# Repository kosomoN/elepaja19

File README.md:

## Lab power supply

This repository contains firmware and PCB designs for a lab power supply designed by Onni Kosomaa, Jere Mielty and Juha Rauhala.

### Repository contents

| Folder                     | Contents                                           |
| -------------------------- | -------------------------------------------------- |
| [components](components)   | Custom KiCad component used in the schematics.     |
| [control_mc](control_mc)   | The regulator MCU firmware.                        |
| [pcb_1](pcb_1)             | The main regulator PCB KiCad project.              |
| [pcb_PiHat](pcb_PiHat)     | The Raspberry Pi Zero extension PCB KiCad project. |
| [pcb_fpanel](pcb_fpanel)   | The main front panel keyboard PCB.                 |
| [pcb_fpanel2](pcb_fpanel2) | The auxiliary front panel keyboard PCB.            |
| [ui](ui)                   | UI software running on the Raspberry Pi.           |

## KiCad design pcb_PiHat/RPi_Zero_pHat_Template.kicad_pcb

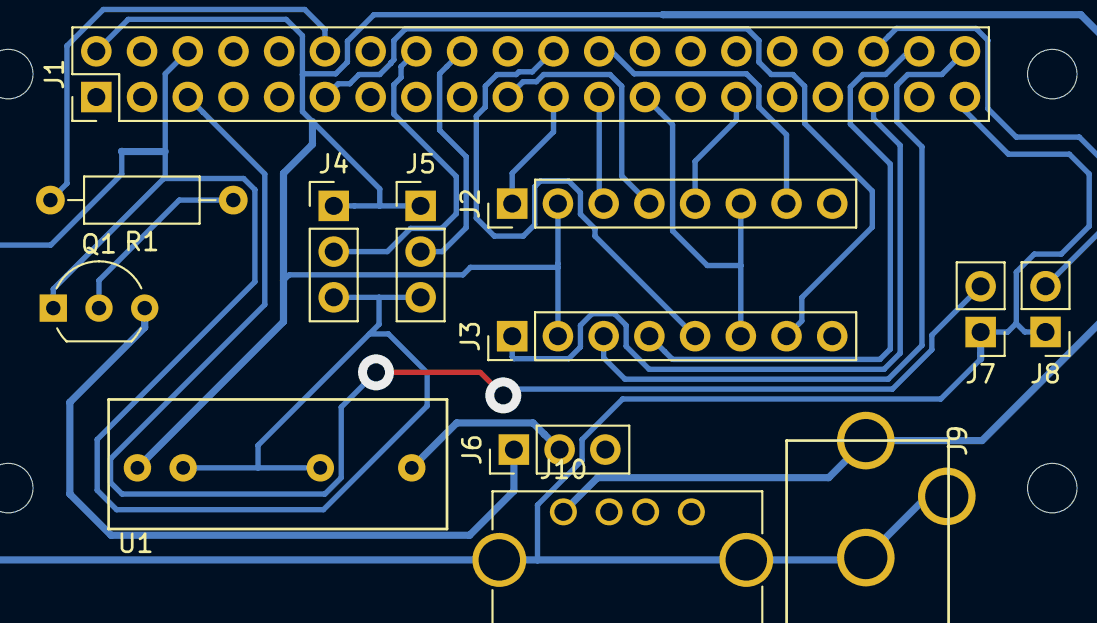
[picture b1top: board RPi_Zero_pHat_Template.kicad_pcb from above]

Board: 2 copper layers, 13 parts (0 on the bottom side), 20 nets.

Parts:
J1: RPi_GPIO; PinHeader_2x20_P2.54mm_Vertical
J2, J3: Isolated_ISP; PinHeader_1x08_P2.54mm_Vertical
J4, J5: Conn_Relay; PinHeader_1x03_P2.54mm_Vertical
J6: Conn_01x03; Pin_Header_Straight_1x03_Pitch2.54mm
J7, J8: Conn_switch; Pin_Header_Straight_1x02_Pitch2.54mm
J9: 5V_in; 5V_power
J10: USB_A
Q1: Q_NPN_EBC; TO-92_Inline_Wide
R1: R; R_Axial_DIN0207_L6.3mm_D2.5mm_P10.16mm_Horizontal
U1: SPUN02L-12

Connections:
GND: J1.6, J1.9, J1.14, J1.20, J1.25, J1.30, J1.34, J1.39, J2.6, J3.6, J4.3, J5.3, J7.1, J8.1, J9.2, J10.4, J10.5, Q1.1, U1.2, U1.5
unnamed: J1.2, J2.2, J3.2, J4.1, J5.1, J9.1, J10.1, U1.1
unnamed: J1.5, J7.2
unnamed: J1.11, J3.7
unnamed: J1.12, R1.2
unnamed: J1.16, J4.2
unnamed: J1.18, J5.2
unnamed: J1.19, J2.4
unnamed: J1.21, J2.1
unnamed: J1.22, J3.5
unnamed: J1.23, J2.3
unnamed: J1.24, J2.7
unnamed: J1.29, J2.5
unnamed: J1.35, J3.1
unnamed: J1.36, J8.2
unnamed: J1.38, J3.4
unnamed: J1.40, J3.3
unnamed: J6.1, Q1.3
unnamed: J6.2, U1.7
unnamed: Q1.2, R1.1

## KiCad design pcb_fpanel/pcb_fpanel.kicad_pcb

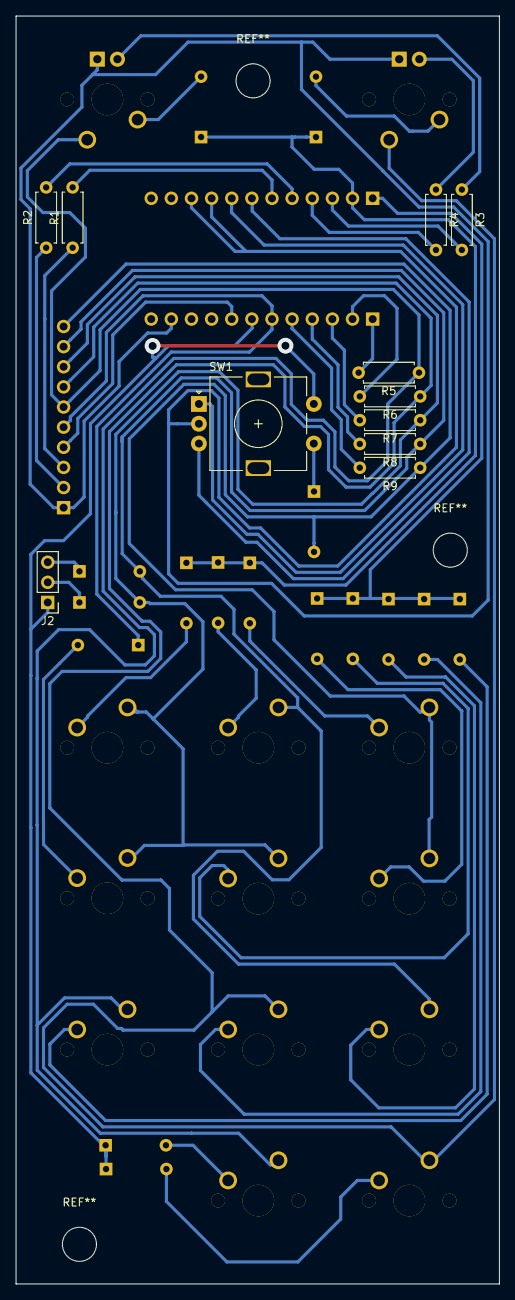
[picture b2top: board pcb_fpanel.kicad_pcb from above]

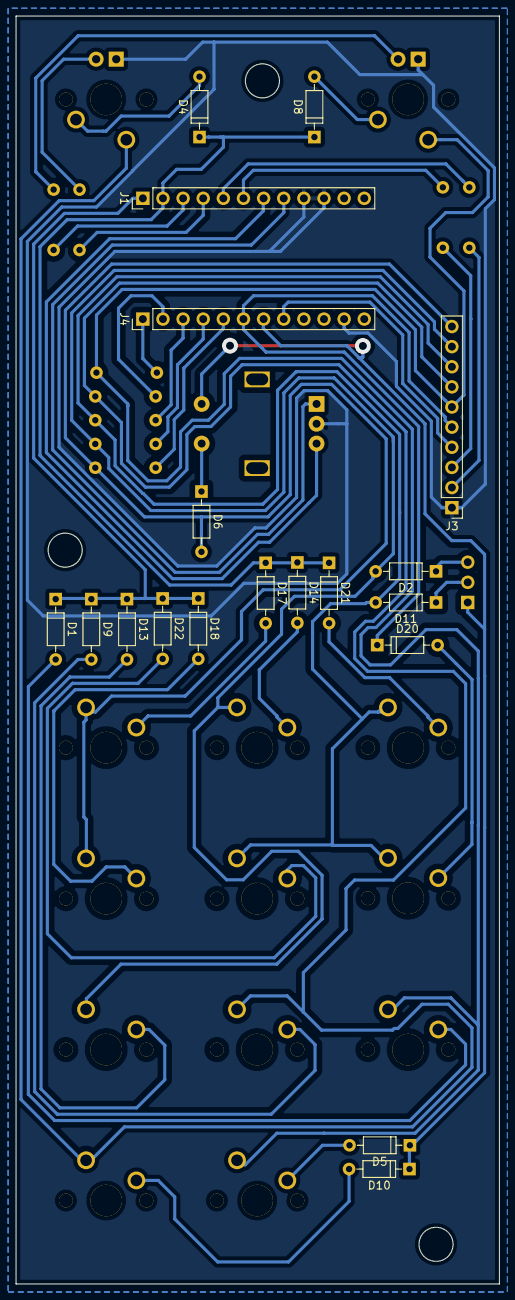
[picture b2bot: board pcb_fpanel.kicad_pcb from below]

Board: 2 copper layers, 61.0 x 160.0 mm, 43 parts (19 on the bottom side), 40 nets.

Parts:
D1, D2, D4, D5, D6, D8, D9, D10, D11, D13, D14, D17, D18, D20, D21, D22: D; D_DO-35_SOD27_P7.62mm_Horizontal
J1, J4: Conn_01x12; Pin_Header_Straight_1x12_Pitch2.54mm
J2: Conn_01x03; Pin_Header_Straight_1x03_Pitch2.54mm
J3: Conn_01x10; Pin_Header_Straight_1x10_Pitch2.54mm
R1, R2, R3, R4, R5, R6, R7, R8, R9: R; R_Axial_DIN0207_L6.3mm_D2.5mm_P7.62mm_Horizontal
SW1: Rotary_Encoder_Switch; RotaryEncoder_Alps_EC11E-Switch_Vertical_H20mm
SW3, SW8: SW_Push_LED; MXOnly-1U
SW4, SW5, SW9, SW10, SW13, SW14, SW17, SW18, SW20, SW21, SW22: SW_Push_LED; MXOnly-1U-NoLED

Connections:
GNDD: J1.9, J1.10, J3.1, J4.11, SW1.C
unnamed: D1.2, SW4.1
unnamed: D2.1, J2.3
unnamed: D4.2, SW3.1
unnamed: D5.2, SW5.1
unnamed: D8.2, SW8.1
unnamed: D9.2, SW9.1
unnamed: D10.2, SW10.1
unnamed: D11.1, J2.2
unnamed: D13.2, SW14.1
unnamed: D14.2, SW13.1
unnamed: D17.2, SW17.1
unnamed: D18.2, SW18.1
unnamed: D20.2, SW20.1
unnamed: D21.2, SW21.1
unnamed: D22.2, SW22.1
unnamed: J1.3, R3.2
unnamed: J1.4, R4.2
unnamed: J1.5, R2.2
unnamed: J1.6, R1.2
unnamed: J1.7, SW1.B
unnamed: J1.8, SW1.A
unnamed: J4.1, R5.2
unnamed: J4.2, R6.2
unnamed: J4.3, R7.2
unnamed: J4.4, R8.2
unnamed: J4.5, R9.2
column_1: J3.6, R5.1, SW4.2, SW5.2, SW8.2
column_2: J3.7, R6.1, SW3.2, SW9.2, SW10.2
column_3: D2.2, J3.9, R8.1, SW13.2, SW14.2
column_4: D6.2, J3.10, R9.1, SW17.2, SW18.2
column_5: D11.2, J3.8, R7.1, SW20.2, SW21.2, SW22.2
encoder_button: D6.1, SW1.S1
led_1: J3.3, R1.1
led_2: J3.2, R2.1
row_1: J3.4, J4.8
row_2: D20.1, J3.5, J4.6
row_3: D4.1, D8.1, D14.1, D17.1, D21.1, J1.2
row_4: D1.1, D9.1, D13.1, D18.1, D22.1, J1.1
row_5: D5.1, D10.1, J2.1, J4.7, SW1.S2

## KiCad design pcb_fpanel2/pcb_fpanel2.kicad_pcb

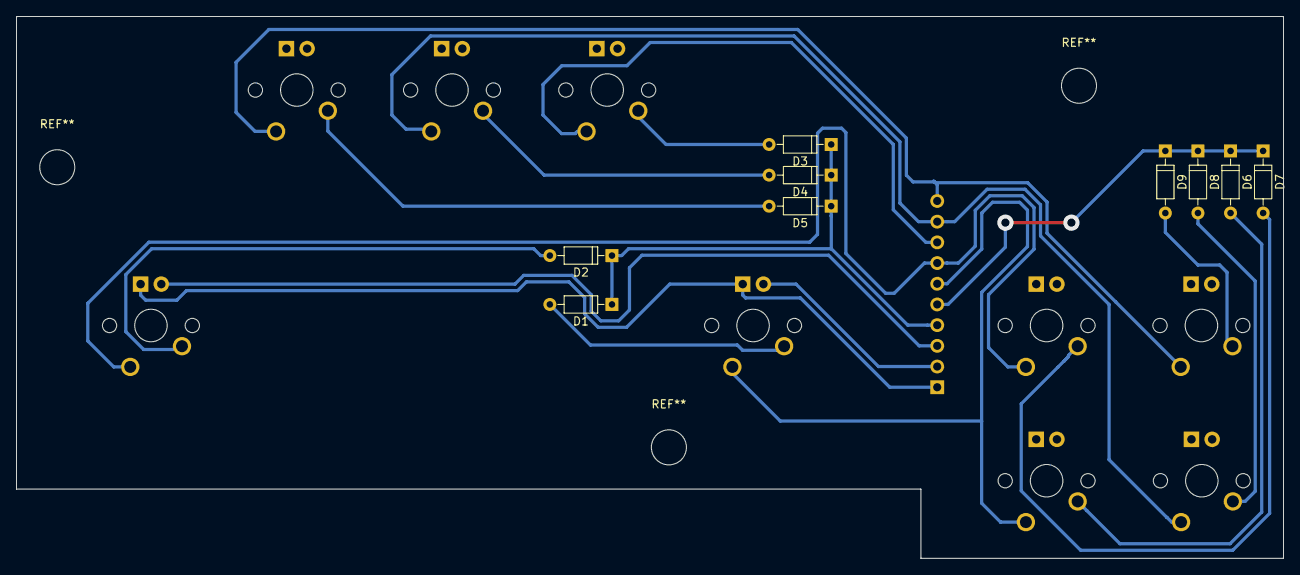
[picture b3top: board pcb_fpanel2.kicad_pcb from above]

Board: 2 copper layers, 155.5 x 66.5 mm, 19 parts (1 on the bottom side), 19 nets.

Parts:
D1, D2, D3, D4, D5, D6, D7, D8, D9: D; D_DO-35_SOD27_P7.62mm_Horizontal
J1: Conn_01x10; Pin_Header_Straight_1x10_Pitch2.54mm
SW1, SW2, SW3, SW4, SW5, SW6, SW7, SW8, SW9: SW_Push_LED; MXOnly-1U

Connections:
GNDD: J1.1, SW1.4, SW2.4
unnamed: D1.2, SW1.1
unnamed: D2.2, SW2.1
unnamed: D3.2, SW3.1
unnamed: D4.2, SW4.1
unnamed: D5.2, SW5.1
unnamed: D6.2, SW6.1
unnamed: D7.2, SW7.1
unnamed: D8.2, SW8.1
unnamed: D9.2, SW9.1
column_1: J1.6, SW1.2, SW6.2
column_2: J1.7, SW2.2, SW7.2
column_3: J1.9, SW4.2, SW8.2
column_4: J1.10, SW5.2, SW9.2
column_5: J1.8, SW3.2
led_1: J1.3, SW2.3
led_2: J1.2, SW1.3
row_1: D1.1, D2.1, D3.1, D4.1, D5.1, J1.4
row_2: D6.1, D7.1, D8.1, D9.1, J1.5

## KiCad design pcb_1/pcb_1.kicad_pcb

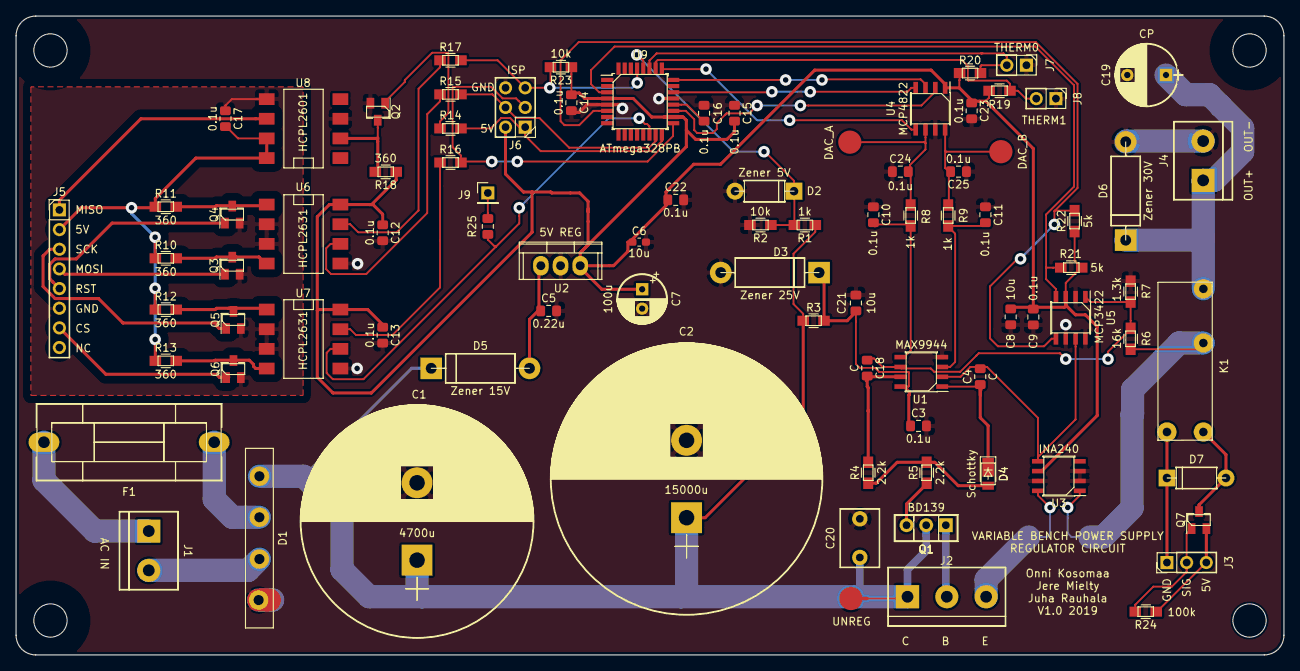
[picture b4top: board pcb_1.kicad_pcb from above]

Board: 2 copper layers, 163.8 x 82.6 mm, 88 parts (1 on the bottom side), 58 nets.

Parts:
C1: 4700u; CP_Radial_D30.0mm_P10.00mm_SnapIn
C2: 15000u; CP_Radial_D35.0mm_P10.00mm_SnapIn
C3, C9, C10, C11, C12, C13, C14, C15, C16, C17, C22, C23, C24, C25: 0.1u; C_0805_2012Metric_Pad1.15x1.40mm_HandSolder
C4, C18: C; C_0805_2012Metric_Pad1.15x1.40mm_HandSolder
C5: 0.22u; C_0805_2012Metric_Pad1.15x1.40mm_HandSolder
C6: 10u; C_0603_1608Metric_Pad1.05x0.95mm_HandSolder
C7: 100u; CP_Radial_D6.3mm_P2.50mm
C8, C21: 10u; C_0805_2012Metric_Pad1.15x1.40mm_HandSolder
C19: CP; CP_Radial_D8.0mm_P5.00mm
C20: C; C_Disc_D7.5mm_W5.0mm_P5.00mm
D1: D_Bridge_+AA-; GBU6D_diode-bridge
D2: Zener 5V; D_DO-41_SOD81_P7.62mm_Horizontal
D3: Zener 25V; D_5W_P12.70mm_Horizontal
D4: Schottky; D_PowerDI-123
D5: Zener 15V; D_5W_P12.70mm_Horizontal
D6: Zener 30V; D_5W_P12.70mm_Horizontal
D7: D; D_DO-41_SOD81_P7.62mm_Horizontal
F1: Fuse; Fuseholder5x20_horiz_SemiClosed_Casing10x25mm
J1, J4: Screw_Terminal_01x02; TerminalBlock_bornier-2_P5.08mm
J2: Screw_Terminal_01x03; TerminalBlock_bornier-3_P5.08mm
J3: Conn_Relay; Pin_Header_Straight_1x03_Pitch2.54mm
J5: Isolated_ISP; Pin_Header_Straight_1x08_Pitch2.54mm
J6: AVR-ISP-6; Pin_Header_Straight_2x03_Pitch2.54mm
J7: THERM0; Pin_Header_Straight_1x02_Pitch2.54mm
J8: THERM1; Pin_Header_Straight_1x02_Pitch2.54mm
J9: CS; PinHeader_1x01_P2.54mm_Vertical
K1: DIPxx-1Axx-11x; PCJ-105D3MH
Q1: BD139; TO-126_Vertical
Q2, Q3, Q4, Q5, Q6, Q7: Q_NMOS_GSD; SuperSOT-3
R1, R8, R9: 1k; R_0805_HandSoldering
R2, R23: 10k; R_0805_HandSoldering
R3, R19, R20: R; R_0805_HandSoldering
R4, R5: 2.2k; R_0805_HandSoldering
R6: 16k; R_0805_HandSoldering
R7: 1.3k; R_0805_HandSoldering
R10, R11, R12, R13, R18: 360; R_0805_HandSoldering
R14, R15, R16, R17: 100; R_0805_HandSoldering
R21, R22: 5k; R_0805_HandSoldering
R24: 100k; R_0805_HandSoldering
R25: 100; R_0805_2012Metric_Pad1.15x1.40mm_HandSolder
Rs1: 0.1; R_2512_HandSoldering
TP1: UNREG; Measurement_Point_Round-SMD-Pad_Big
TP2: DACa; Measurement_Point_Round-SMD-Pad_Big
TP3: DACb; Measurement_Point_Round-SMD-Pad_Big
U1: MAX9944; SOIC-8_3.9x4.9mm_Pitch1.27mm
U2: 5V REG; TO-220
U3: INA240; SOIC-8_3.9x4.9mm_Pitch1.27mm
U4: MCP4822; SOIC-8_3.9x4.9mm_Pitch1.27mm
U5: MCP3422; SOIC-8_3.9x4.9mm_Pitch1.27mm
U6, U7: HCPL2631; HCPL2631SD
U8: HCPL2601; HCPL2631SD
U9: ATmega328PB; TQFP-32_7x7mm_Pitch0.8mm

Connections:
+5V: C6.1, C7.1, C8.1, C9.2, C12.1, C13.1, C14.1, C15.2, C22.1, C23.1, J6.2, R18.1, R19.1, R20.1, R21.1, R22.1, R23.1, U2.3, U3.6, U4.1, U5.3, U6.8, U7.8, U9.4, U9.18
ADC_SCL: R22.2, U5.5, U9.6
ADC_SDA: R21.2, U5.4, U9.3
DAC_CS: U4.2, U9.19
DAC_LDAC: U4.5, U9.25
DAC_SCK: U4.3, U9.24
DAC_SDI: U4.4, U9.22
GNDA: C1.2, C2.2, C3.2, C5.2, C6.2, C7.2, C8.2, C9.1, C10.1, C11.1, C12.2, C13.2, C14.2, C15.1, C16.2, C19.2, C20.2, C21.2, C22.2, C23.2, C24.1, C25.1, D1.4, D2.2, D3.2, D6.2, J4.2, J6.6, J7.1, J8.1, Q2.2, R2.2, R7.2, U1.4, U2.2, U3.2, U3.3, U3.7, U4.7, U5.2, U5.6, U5.8, U6.5, U7.5, U8.3, U9.5, U9.21
Imon: C4.2, U1.2, U3.5, U5.7
Iset: C11.2, R9.1, U1.3
unnamed: C1.1, C2.1, C20.1, D1.1, D5.1, J2.1, Q1.2, R1.1, R3.1, TP1.1
unnamed: C4.1, D4.1, U1.1
unnamed: C5.1, D5.2, U2.1
unnamed: C16.1, U9.20
unnamed: C17.1, J5.6, Q3.2, Q4.2, Q5.2, Q6.2, U6.2, U6.3, U7.2, U7.3, U8.5
unnamed: C17.2, J5.2, R10.1, R11.1, R12.1, R13.1, U8.7, U8.8
unnamed: C18.2, R4.2, U1.7
unnamed: C19.1, D6.1, J4.1, K1.7
unnamed: C3.1, C21.1, D3.1, R3.2, U1.8
unnamed: C24.2, R8.2, TP2.1, U4.6
unnamed: C25.2, R9.2, TP3.1, U4.8
unnamed: D1.2, F1.1
unnamed: D1.3, J1.2
unnamed: D4.2, R4.1, R5.2
unnamed: D7.1, J3.1, K1.2
unnamed: D7.2, K1.6, Q7.3
unnamed: F1.2, J1.1
unnamed: J2.2, Q1.1
unnamed: J2.3, Rs1.1, U3.8
unnamed: J3.2, Q7.1, R24.2
unnamed: J3.3, Q7.2, R24.1
unnamed: J5.1, U8.6
unnamed: J5.3, Q5.1
unnamed: J5.4, Q3.1
unnamed: J5.5, Q4.1
unnamed: J5.7, Q6.1
unnamed: J6.1, R14.2, U9.16
unnamed: J6.3, R16.2, U9.17
unnamed: J6.4, R15.2, U9.15
unnamed: J6.5, R17.2, R23.2, U9.29
unnamed: J7.2, R20.2, U9.27
unnamed: J8.2, R19.2, U9.26
unnamed: J9.1, R25.1
unnamed: K1.1, R6.1, Rs1.2, U3.1
unnamed: Q1.3, R5.1
unnamed: Q2.3, R18.2, U8.2
unnamed: Q3.3, R10.2, U6.4
unnamed: Q4.3, R11.2, U6.1
unnamed: Q5.3, R12.2, U7.1
unnamed: Q6.3, R13.2, U7.4
SLAVE_CS: R25.2, U7.6, U9.14
SLAVE_MISO: Q2.1, R14.1
SLAVE_MOSI: R15.1, U6.6
SLAVE_RESET: R17.1, U6.7
SLAVE_SCK: R16.1, U7.7
UNREG_MON: D2.1, R1.2, R2.1, U9.28
Vmon: C18.1, R6.2, R7.1, U1.6, U5.1
Vset: C10.2, R8.1, U1.5

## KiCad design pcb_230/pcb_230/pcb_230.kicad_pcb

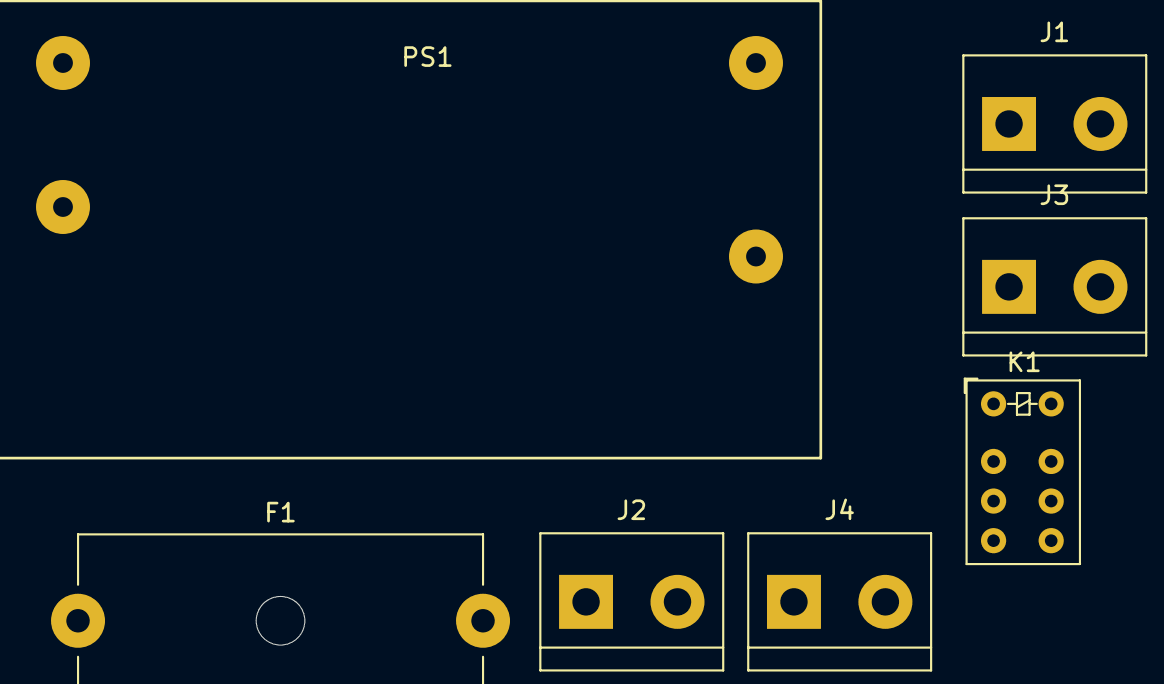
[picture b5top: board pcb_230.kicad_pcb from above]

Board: 2 copper layers, 7 parts (0 on the bottom side), 8 nets, no tracks yet.

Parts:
F1: Fuse; Fuseholder5x20_horiz_open_Schurter_0031_8201
J1, J2, J3, J4: Screw_Terminal_01x02; TerminalBlock_bornier-2_P5.08mm
K1: AZ850P1-x; Relay_DPDT_AXICOM_IMSeries_Pitch3.2mm
PS1: HLK-PM01; IRM-05_ACDC

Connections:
unnamed: F1.1, K1.3, PS1.1
unnamed: F1.2, J1.2
unnamed: J1.1, K1.8, PS1.2
unnamed: J2.2, K1.1
unnamed: J3.1, PS1.4
unnamed: J3.2, PS1.3
unnamed: J4.1, K1.4
unnamed: J4.2, K1.7

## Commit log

2019-10-18 KiCad.gitignore lisätty
2019-10-18 KiCad projekti aloitettu
2019-10-18 Komponenttitiedostot lisätty
2019-10-19 Transistor_BJT-file poistettu tarpeettomana
2019-10-19 Mittauspinnit lisätty
2019-10-19 AC-input lisätty Footprintit mikropiireille
2019-10-19 -Tasasuuntaajalle footprint footprints kansiossa -Oparille lisätty kapasitpanssipaikkoja
2019-10-20 pcb suunniteltu
2019-10-20 .gitignore tiedoston nimi korjattu
2019-10-20 Muuta Library pathit suhteellisiksi
2019-10-22 Oparin regu vaihdettu ja konkkien footprintejä muutettu
2019-10-22 UI Raylib pohja lisätty
    Lisää Makefile:in Raspberry PI:lle, Linuxille sekä Windowsille.
    Lisää myös Visual Studio 2017 projektin.
    Makefile sekä VS2017 etsii oletuksena Raylibiä
    elepaja19/../raylib kansiosta.
2019-10-24 Traceja paksunnettu
2019-10-27 Säätömikrokontrollerin Makefile-pohja
2019-10-28 INA240 kotelo vaihdettu ja toinen vastaava vahvistin poistettu
2019-10-29 Footprintteja muutettu oikeiksi
2019-10-30 pcb:ssa nyt smd- ja tht-komponentit eri puolilla
2019-10-31 30.10 syövytetty pcb
2019-11-10 control_mc: Add communicat:ion pins configuration
2019-11-12 pcb: Add first version with a MCU
    Also update the Kicad project to Kicad version 5
2019-11-13 pcb: Add relay and filtering capacitors
2019-11-14 pcb: Fix mismatching global labels
    Also add connections for thermistors.
2019-11-14 pcb: Add Zener regulator to op-amp supply
2019-11-16 control_mc: Fix line endings in constants.h
2019-11-16 control_mc: Add DAC interfacing code
2019-11-16 Footprintit asetettu ja pcb layout aloitettu
2019-11-16 Footprintit lisätty ja pcb-layout aloitettu
2019-11-16 Komponentit aseteltu paikoilleen ja vähän traceja vedelty
2019-11-17 pcb: Releen ohjauspiiri lisätty
2019-11-17 pcb: Kaikki vedot tehty
2019-11-17 pcb_PiHat: Pi Hatin ensimmäinen versio lisätty
2019-11-17 pcb_PiHat: Relee headeri lisätty
2019-11-17 Toinen konkka lisätty
2019-11-17 pcb: Rescue kirjasto poistettu
2019-11-17 pcb: Suodatuskonkat ja kiinnitysreiät lisätty
2019-11-17 pcb: Kulmat pyöristetty
2019-11-18 NMOS-symbolit muutettu
2019-11-18 pcb: Silkscreeniä päivitetty
2019-11-18 pcb_PiHat: Toisen releen headeri lisätty
2019-11-18 pcb: Gerber tiedostot lisätty
2019-11-18 pcb: Kondensaattoreiden footprintit muuttettu
2019-11-19 pcb: Optcouplereitten virranrajotinvastkset muutettu
2019-11-20 frontpanel pcb aloitettu
2019-11-23 Frontpanel pcb valmis
2019-11-24 Frontpanel pcb korjaus: led-napit käännetty ja yhteensopivuus arduino pro micron kanssa
2019-11-24 Interrupt pinnit muutettu PC->Ext
2019-11-24 fpanel1 ja fpanel2 välisen liittimen pin-järjestys korjattu vastaamaan toisiaan
2019-11-25 Näppäinmatriisin srakkeille lisätty etuvastukset
2019-11-25 Reikien siirtelyä
2019-11-25 Näppäinten sijainnit ja footprintit päivitetty
2019-11-25 pcb_fpanel2: Tekijät-teksti lisätty footprinttinä
2019-11-26 pcb_fpanel: Käyttämättömät footprint kirjastot poistettu
2019-11-26 pcb_fpanel: Käyttämättömien ledien reiät poistettu
2019-11-26 pcb_fpanel: Kytkimien footprintien reikätyyppejä muutettu
2019-12-01 control_mc: Add AVR fuse Makefile target
2019-12-01 ui: Add SPI interface through wiringPi
2019-12-01 control_mc: Add slave SPI protocol
2019-12-02 Merge branch 'master' of https://github.com/kosomoN/elepaja19.git
    # Conflicts:
    # pcb_fpanel/pcb_fpanel.kicad_pcb
2019-12-05 raspi hat toteutettu versio
2019-12-12 ui: Add a crude functional UI
2019-12-12 control_mc: Fix SPI packet processing and add avr-i2c
2019-12-14 pcbs: Remove unnecessary files
2019-12-16 control_mc: Finalize ADC reading
2019-12-16 ui: Improve key press handling
2019-12-28 ui: Add crude two-point calibration UI
2020-01-13 Add TOC to README.md
